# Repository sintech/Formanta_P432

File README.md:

# Форманта П432
инструкция ([djvu](docs/Formanta%20P432%20Users%20manual.djvu) | [pdf](docs/Formanta%20P432%20Users%20manual.pdf)), [схемы](schematic), [прошивки](roms) и [эмулятор](src).

Устройство для проверки узла генераторов - [Cхема PDF](kicad/OscTester/OscTester.pdf)

Инструкция по доработке узла генераторов до последней известной версии - [PDF](docs/Oscillator_board_upgrade_tips.pdf)

# Formanta P432 # 
[Manual](docs/Formanta%20P432%20Users%20manual.pdf), [schematic diagrams](schematic), [ROM dumps](roms) and [emulator](src).

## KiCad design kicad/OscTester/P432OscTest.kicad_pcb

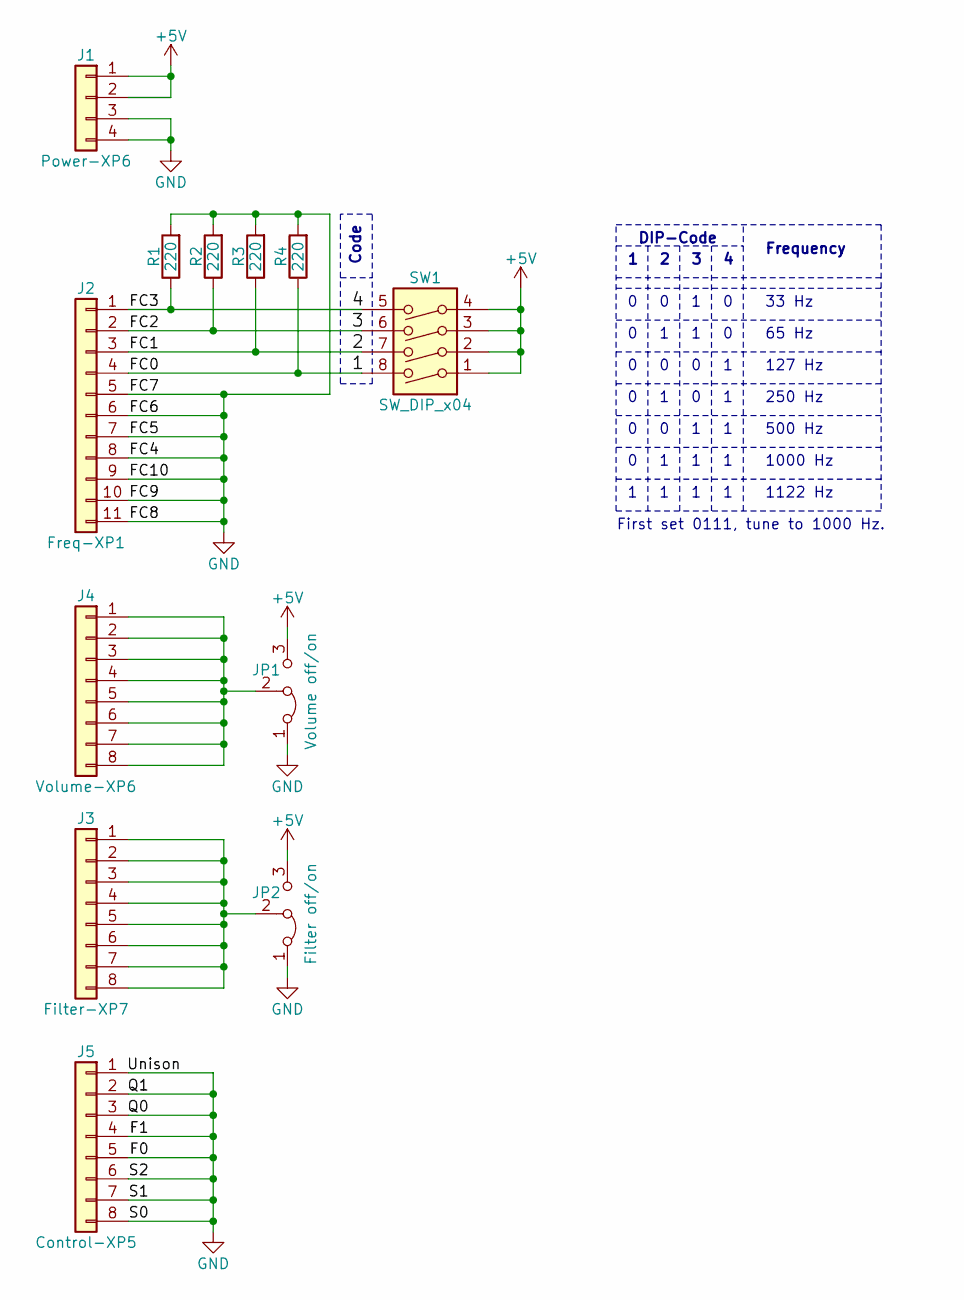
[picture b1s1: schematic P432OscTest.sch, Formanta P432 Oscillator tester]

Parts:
J1: Power-XP6; PinSocket_1x04_P2.54mm_Vertical
J2: Freq-XP1; PinSocket_1x11_P2.54mm_Vertical
J3: Filter-XP7; PinSocket_1x08_P2.54mm_Vertical
J4: Volume-XP6; PinSocket_1x08_P2.54mm_Vertical
J5: Control-XP5; PinSocket_1x08_P2.54mm_Vertical
JP1: Volume off/on; PinHeader_1x03_P2.54mm_Vertical
JP2: Filter off/on; PinHeader_1x03_P2.54mm_Vertical
R1, R2, R3, R4: 220; R_1206_3216Metric
SW1: SW_DIP_x04; SW_DIP_SPSTx04_Slide_9.78x12.34mm_W7.62mm_P2.54mm

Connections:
+5V: J1.1, J1.2, JP1.3 (B), JP2.3 (B), SW1.1, SW1.2, SW1.3, SW1.4
/1: J2.4, R4.1, SW1.8
/2: J2.3, R3.1, SW1.7
/3: J2.2, R2.1, SW1.6
/4: J2.1, R1.1, SW1.5
GND: J1.3, J1.4, J2.5, J2.6, J2.7, J2.8, J2.9, J2.10, J2.11, J5.1, J5.2, J5.3, J5.4, J5.5, J5.6, J5.7, J5.8, JP1.1 (A), JP2.1 (A), R1.2, R2.2, R3.2, R4.2
unnamed: J3.1, J3.2, J3.3, J3.4, J3.5, J3.6, J3.7, J3.8, JP2.2 (C)
unnamed: J4.1, J4.2, J4.3, J4.4, J4.5, J4.6, J4.7, J4.8, JP1.2 (C)

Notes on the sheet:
Frequency
33 Hz
65 Hz
127 Hz
250 Hz
500 Hz
1000 Hz
1122 Hz
First set 0111, tune to 1000 Hz.
DIP-Code
Code

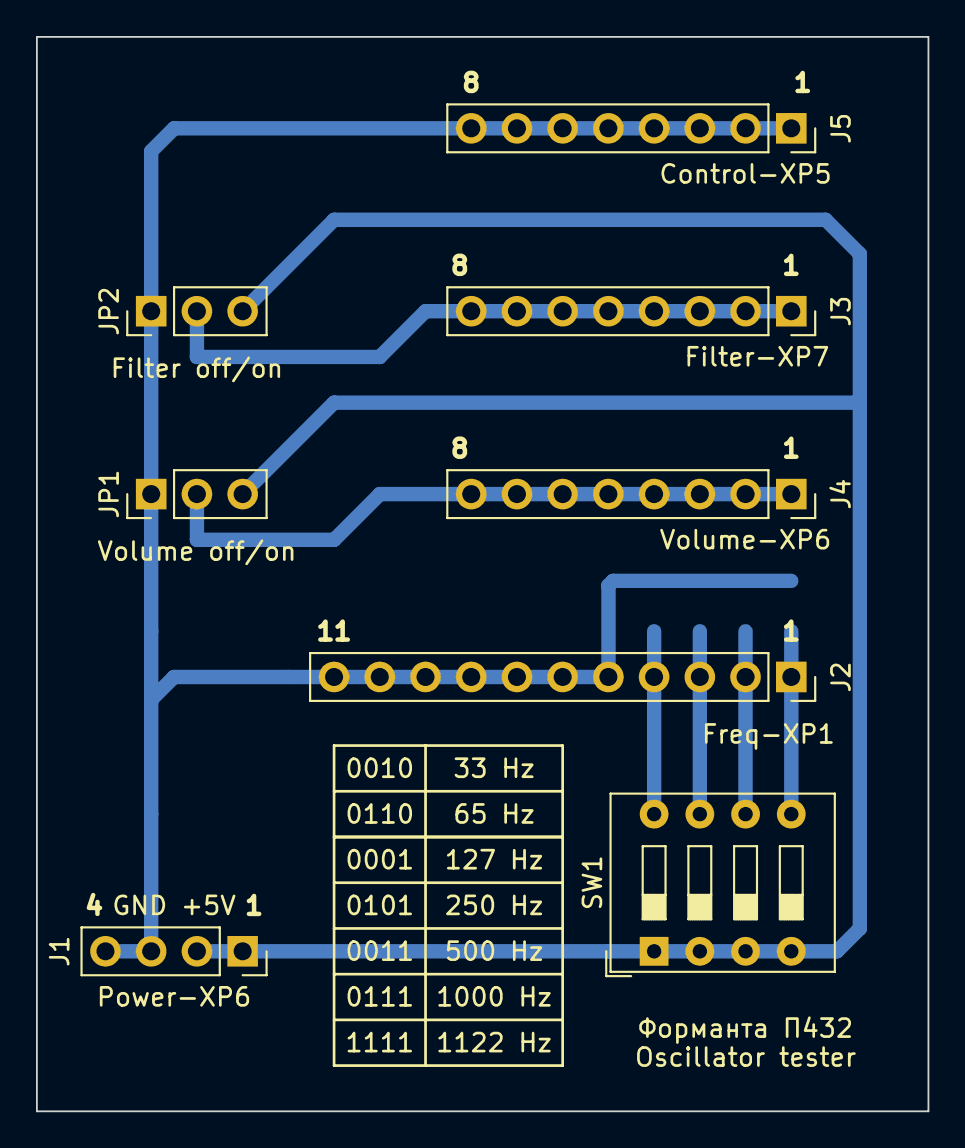
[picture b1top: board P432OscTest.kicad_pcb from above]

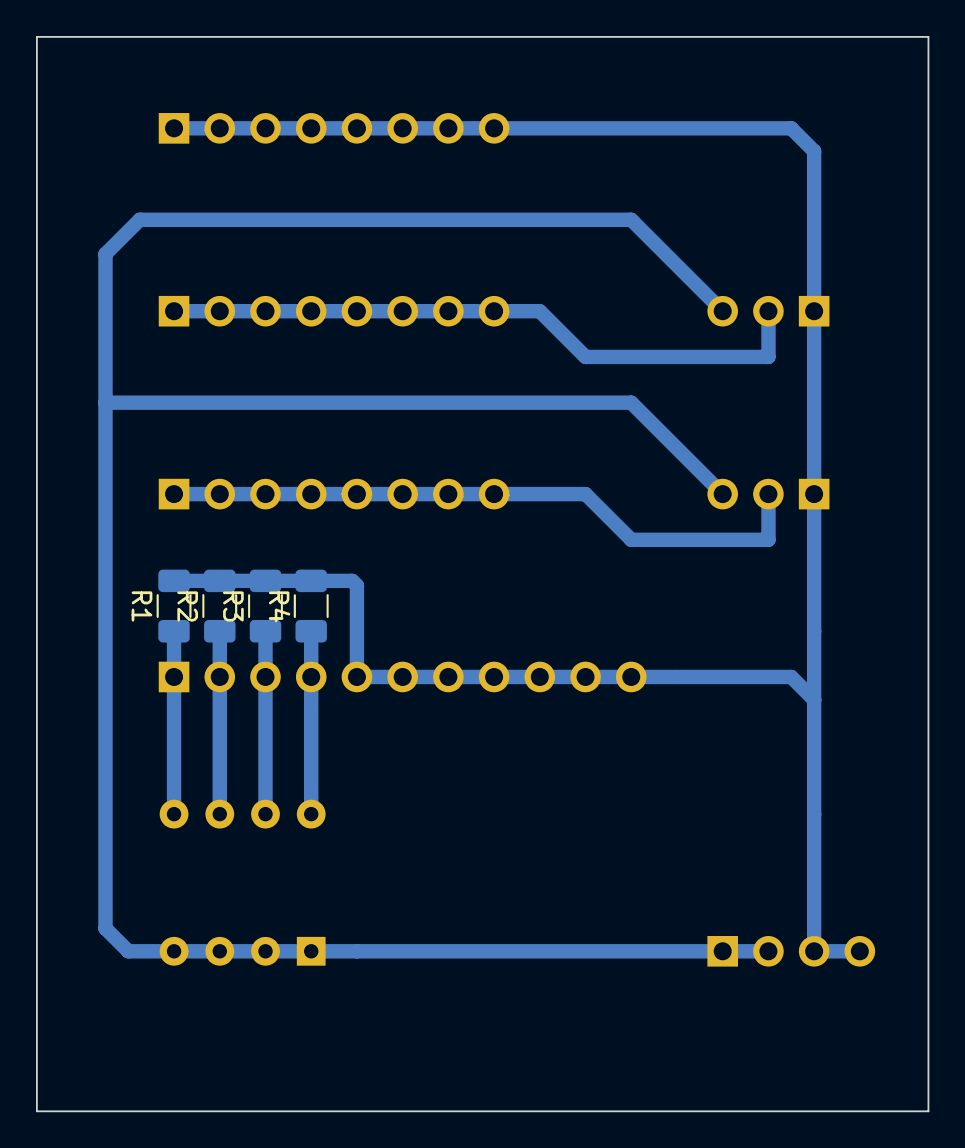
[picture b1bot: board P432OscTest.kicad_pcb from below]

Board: 2 copper layers, 49.5 x 59.7 mm, 12 parts (4 on the bottom side), 8 nets.

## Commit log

2020-01-04 initial files
2020-03-31 Oscillator board upgrade tips
2020-03-31 Oscillator tester
2020-03-31 pcb fix
2020-04-21 Unison bit set to 0 to test all 8 voices
2020-04-29 Freq values changed to the correct ones.
